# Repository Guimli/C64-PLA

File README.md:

# Another C64 PLA

And yes... Another PLA for the C64. There are already too many available. But I thought they were all too big and ugly.
This version uses SOIC format components. This reduces the size of the PCB to that of a standard DIP28. And the components used are still produced, and can therefore be bought from a supplier.
To design this PLA, I used Lubomir Rintel's excellent work: https://github.com/lkundrak/yac64pla

Approximate cost for one C64-PLA (costs can reduced if you build several modules) :

(Be careful to select ATF22LV10s with an access time of 30ns. The Commodore 64 does not appreciate components that are too fast...)

- 2 x ATF22LV10CQZ-30SU  : 8.16 €
- PCB (with Shipping cost) : 23 €
- 2 x 14 pin P2.54 : 4.36 €

Total : 35.52 €

I can sell you this module if you don't want to assemble it yourself. Contact me on guimli@free.fr

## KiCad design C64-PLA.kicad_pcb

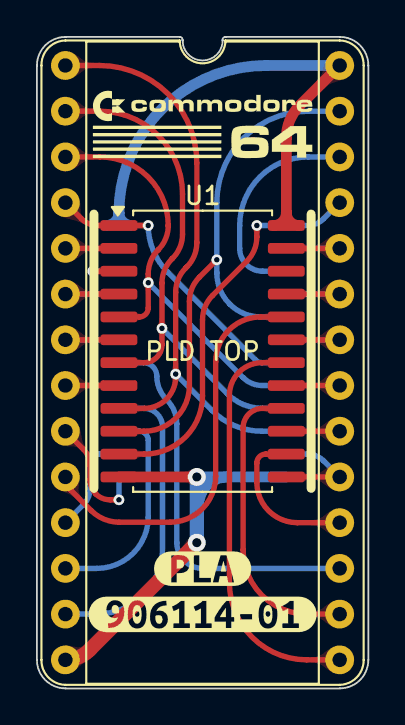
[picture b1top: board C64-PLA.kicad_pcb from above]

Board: 2 copper layers, 18.4 x 36.2 mm, 5 parts (1 on the bottom side), 29 nets.

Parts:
U1, U2: ATF22V10C; SOIC-24W_7.5x15.4mm_P1.27mm
U3: C64_PLA; DIP-28_W15.24mm_Socket
kibuzzard-6781C1DF: G***; kibuzzard-6781C1DF
kibuzzard-6781C1F4: G***; kibuzzard-6781C1F4

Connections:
/A12: U1.10 (I9), U2.5 (I4), U3.27 (I8/A12)
/A13: U1.7 (I6), U2.9 (I8), U3.2 (I7/A13)
/A14: U1.5 (I4), U2.8 (I7), U3.3 (I6/A14)
/A15: U1.1 (I0/CLK), U2.7 (I6), U3.4 (I5/A15)
/BA: U2.3 (I2), U3.26 (I9/BA)
/FE: U1.9 (I8), U2.10 (I9), U3.1 (FE/NC)
/GR/~W: U2.16 (I/O14), U3.13 (F4/GR/~W)
/R/~W: U1.23 (I/O21), U2.2 (I1), U3.24 (I11/R/~W)
/TCR: U1.3 (I2), U2.22 (I/O20)
/VA12: U1.15 (I/O13), U3.20 (I15/VA12)
/VA13: U1.17 (I/O15), U3.21 (I14/VA13)
/~AEC: U1.11 (I10), U2.1 (I0/CLK), U3.25 (I10/~AEC)
/~BASIC: U2.18 (I/O16), U3.17 (F1/~BASIC)
/~CASRAM: U1.14 (I/O12), U3.18 (F0/~CASRAM)
/~CAS: U2.13 (I11), U3.9 (I0/~CAS)
/~CHAREN: U1.4 (I3/PD), U2.21 (I/O19), U3.6 (I3/~CHAREN)
/~CHAROM: U1.18 (I/O16), U3.15 (F3/~CHAROM)
/~EXROM: U1.21 (I/O19), U2.4 (I3/PD), U3.23 (I12/~EXROM)
/~GAME: U1.19 (I/O17), U2.6 (I5), U3.22 (I13/~GAME)
/~IRAM: U1.6 (I5), U2.19 (I/O17), U3.7 (I2/~IRAM)
/~I/O: U2.15 (I/O13), U3.12 (F5/~I/O)
/~KERNAL: U1.16 (I/O14), U3.16 (F2/~KERNAL)
/~LORAM: U1.8 (I7), U2.17 (I/O15), U3.8 (I1/~LORAM)
/~OE: U1.13 (I11), U2.11 (I10), U3.19 (~OE)
/~ROMH: U1.20 (I/O18), U3.10 (F7/~ROMH)
/~ROML: U2.14 (I/O12), U3.11 (F6/~ROML)
/~VA14: U1.2 (I1), U3.5 (I4/~VA14)
GND: U1.12 (GND), U2.12 (GND), U3.14 (VSS)
VCC: U1.24 (VCC), U2.24 (VCC), U3.28 (VCC)

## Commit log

2025-03-10 Remove backup
